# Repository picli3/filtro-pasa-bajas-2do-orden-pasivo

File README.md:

# filtro-pasa-bajas-2do-orden-pasivo

Filtro pasa bajas pasivo de segundo orden, orientado a separar frecuencias en aplicaciones de audio o acondicionamiento analógico.

## Qué incluye
- esquemáticos o archivos de diseño en KiCad
- PCB o documentación asociada
- base reutilizable para análisis, fabricación o mejora del proyecto

## Propósito general
Este repositorio busca concentrar el diseño de hardware del proyecto en un formato editable y reutilizable, facilitando pruebas, documentación y futuras iteraciones del circuito.

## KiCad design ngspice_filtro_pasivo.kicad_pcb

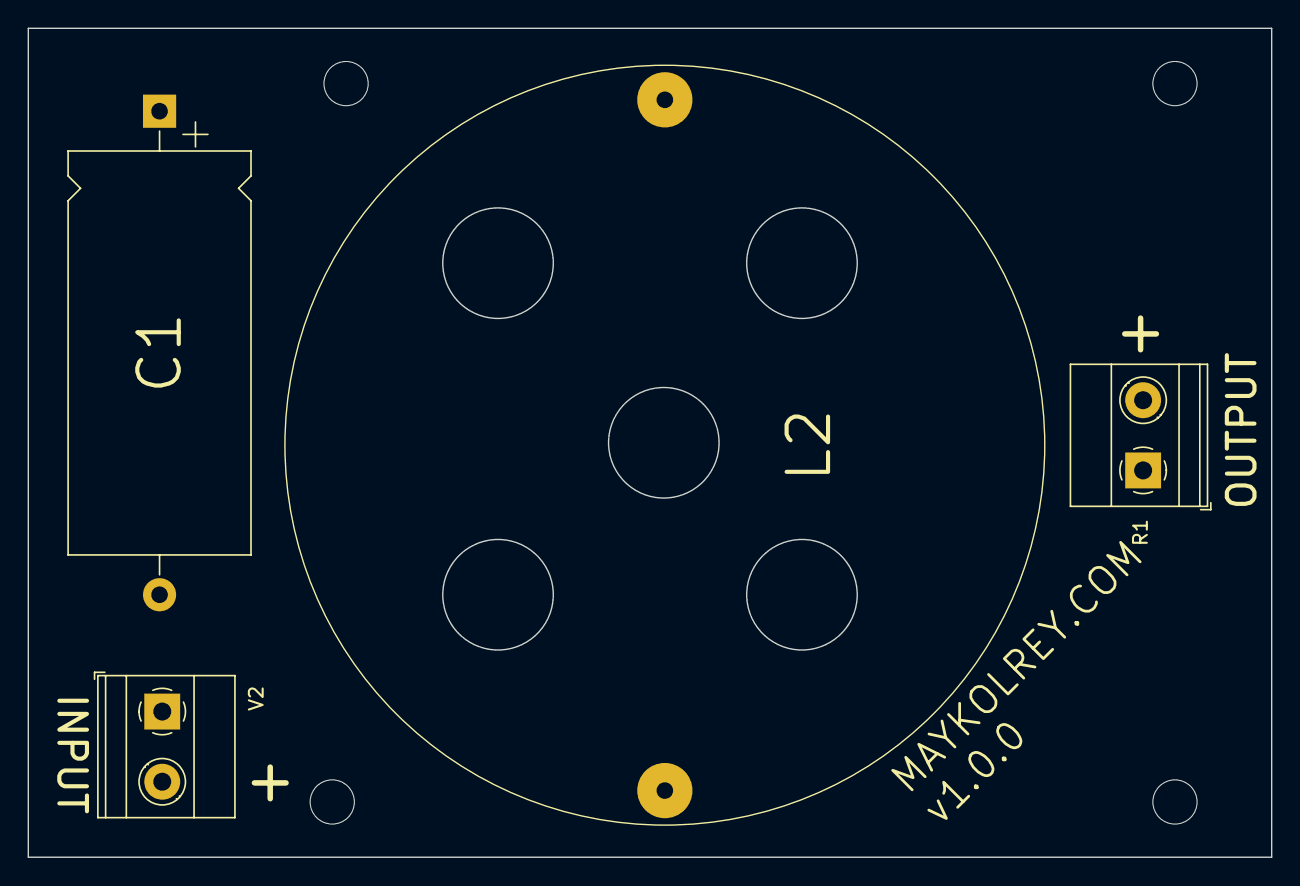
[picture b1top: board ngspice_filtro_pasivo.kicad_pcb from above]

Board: 2 copper layers, 90.0 x 60.0 mm, 8 parts (0 on the bottom side), 3 nets, no tracks yet.

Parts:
C1: c=56u; CP_Axial_L29.0mm_D13.0mm_P35.00mm_Horizontal
H1, H2, H3, H4: MountingHole; MountingHole_3.2mm_M3_DIN965
L2: l=1.8m; Inductor_3055
R1: r=8; TerminalBlock_Phoenix_MKDS-1,5-2-5.08_1x02_P5.08mm_Horizont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
V2: 50Vac; TerminalBlock_Phoenix_MKDS-1,5-2-5.08_1x02_P5.08mm_Horizont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

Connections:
/vi: L2.1, V2.2
/vo: C1.1, L2.2, R1.2
GND: C1.2, R1.1, V2.1

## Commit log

2023-04-30 primera version sin probar
2023-04-30 agregando documentos de fabricacion
2023-04-30 se me olvida actualizar el PDB antes del ultimo commit
2026-04-29 Agrega README con descripción inicial del proyecto
